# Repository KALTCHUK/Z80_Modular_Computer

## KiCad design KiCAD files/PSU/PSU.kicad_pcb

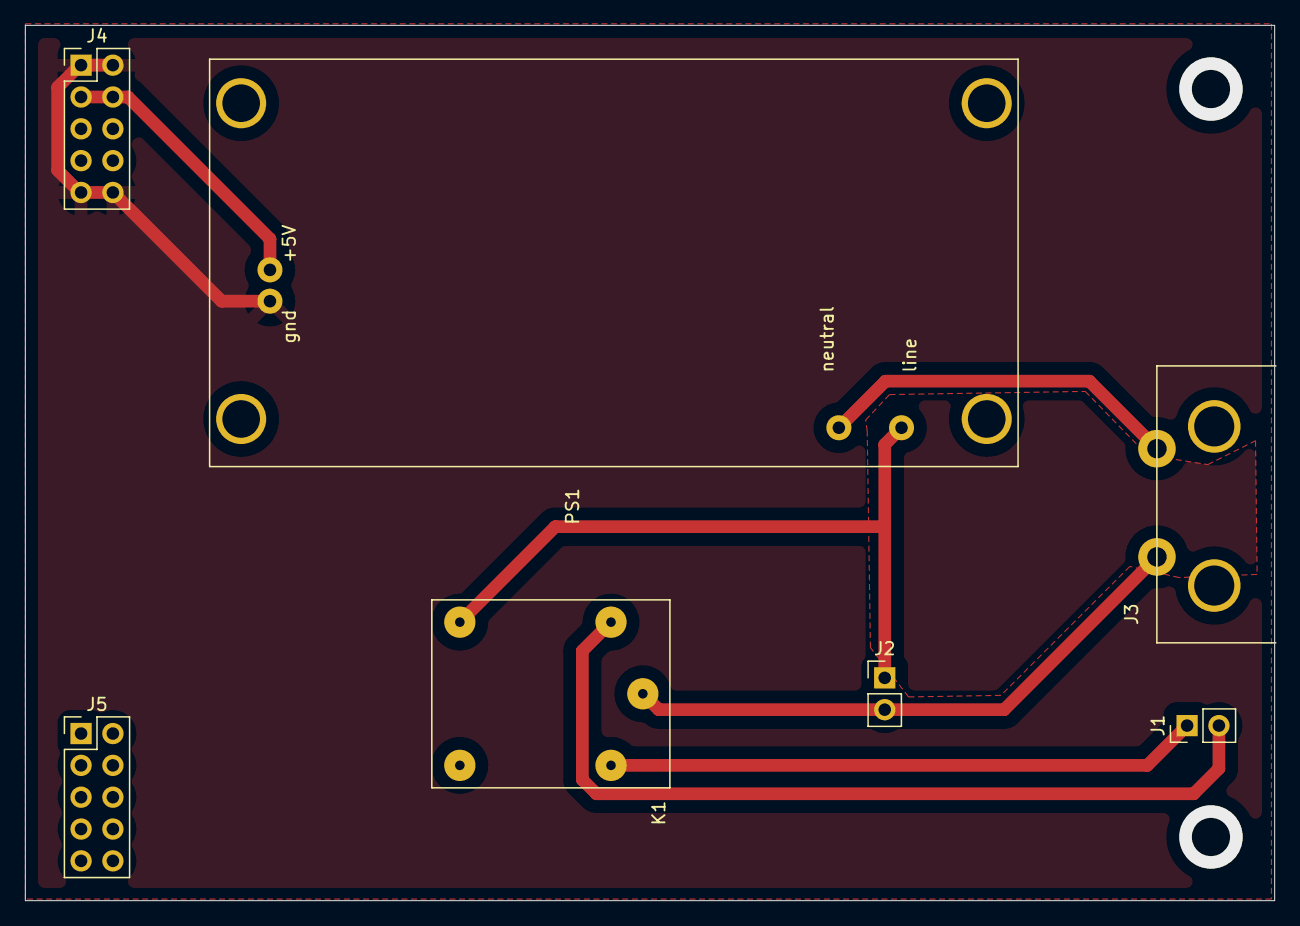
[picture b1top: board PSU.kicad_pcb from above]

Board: 2 copper layers, 99.7 x 69.8 mm, 7 parts (0 on the bottom side), 7 nets.

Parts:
J1: Ext power on; PinHeader_1x02_P2.54mm_Vertical
J2: Power switch; PinHeader_1x02_P2.54mm_Vertical
J3: Mains; IEC60320_2pin
J4: Power bus; PinHeader_2x05_P2.54mm_Vertical
J5: Mech support; PinHeader_2x05_P2.54mm_Vertical
K1: SRD-05VDC-SL-C; Relay_SPDT_Songel-15x19mm
PS1: XPJ-01B_5V_10W; Converter_ACDC_5V_10W_XPJ-01B

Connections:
GNDREF: J4.1, J4.2, J4.9, J4.10, PS1.3 (-Vo)
LINE: J2.2, J3.2, K1.5
NEUT: J3.1, PS1.1 (AC/N)
unnamed: J1.1, K1.4
unnamed: J1.2, K1.3
unnamed: J2.1, K1.1, PS1.2 (AC/L)
unnamed: J4.3, J4.4, PS1.4 (+Vo)

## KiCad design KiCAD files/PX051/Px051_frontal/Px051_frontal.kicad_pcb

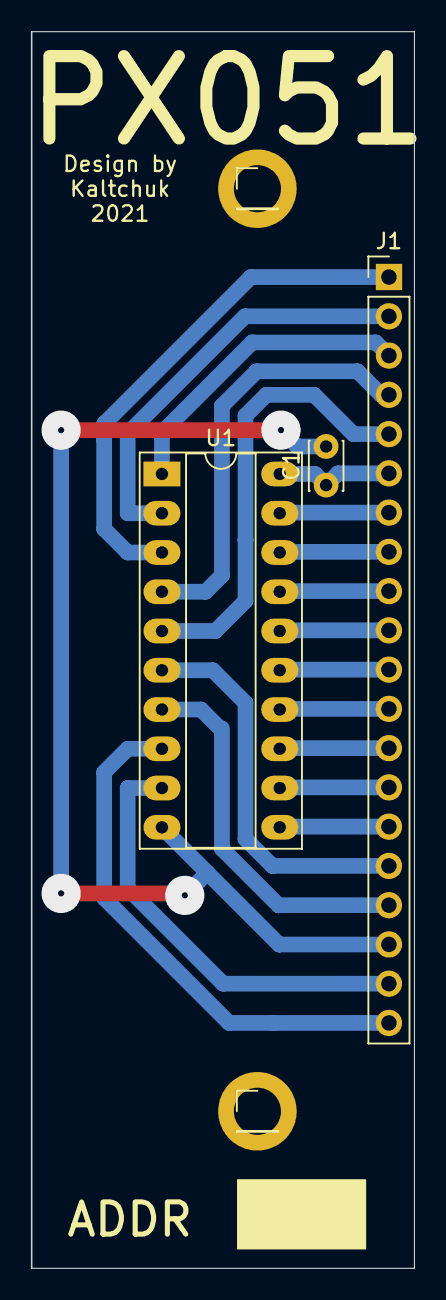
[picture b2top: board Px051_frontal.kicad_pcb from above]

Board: 2 copper layers, 24.8 x 80.0 mm, 5 parts (0 on the bottom side), 20 nets.

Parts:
C1: 10nF; C_Disc_D3.0mm_W2.0mm_P2.50mm
J1: Conn_01x20_Male; PinHeader_1x20_P2.54mm_Vertical
J7, J8: fixing bolt; PinHeader_1x01_P2.54mm_Vertical
U1: AT89C4051-24P; DIP-20_W7.62mm_Socket_LongPads

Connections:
GND: C1.2, J1.18, U1.10 (GND)
unnamed: C1.1, J1.6, U1.20 (VCC)
unnamed: J1.1, U1.3 (P3.1)
unnamed: J1.2, U1.2 (P3.0)
unnamed: J1.3, U1.1 (RST/VPP)
unnamed: J1.4, U1.4 (XTAL2)
unnamed: J1.5, U1.5 (XTAL1)
unnamed: J1.7, U1.19 (P1.7)
unnamed: J1.8, U1.18 (P1.6)
unnamed: J1.9, U1.17 (P1.5)
unnamed: J1.10, U1.16 (P1.4)
unnamed: J1.11, U1.15 (P1.3)
unnamed: J1.12, U1.14 (P1.2)
unnamed: J1.13, U1.13 (P1.1)
unnamed: J1.14, U1.12 (P1.0)
unnamed: J1.15, U1.11 (P3.7)
unnamed: J1.16, U1.6 (P3.2)
unnamed: J1.17, U1.7 (P3.3)
unnamed: J1.19, U1.9 (P3.5)
unnamed: J1.20, U1.8 (P3.4)

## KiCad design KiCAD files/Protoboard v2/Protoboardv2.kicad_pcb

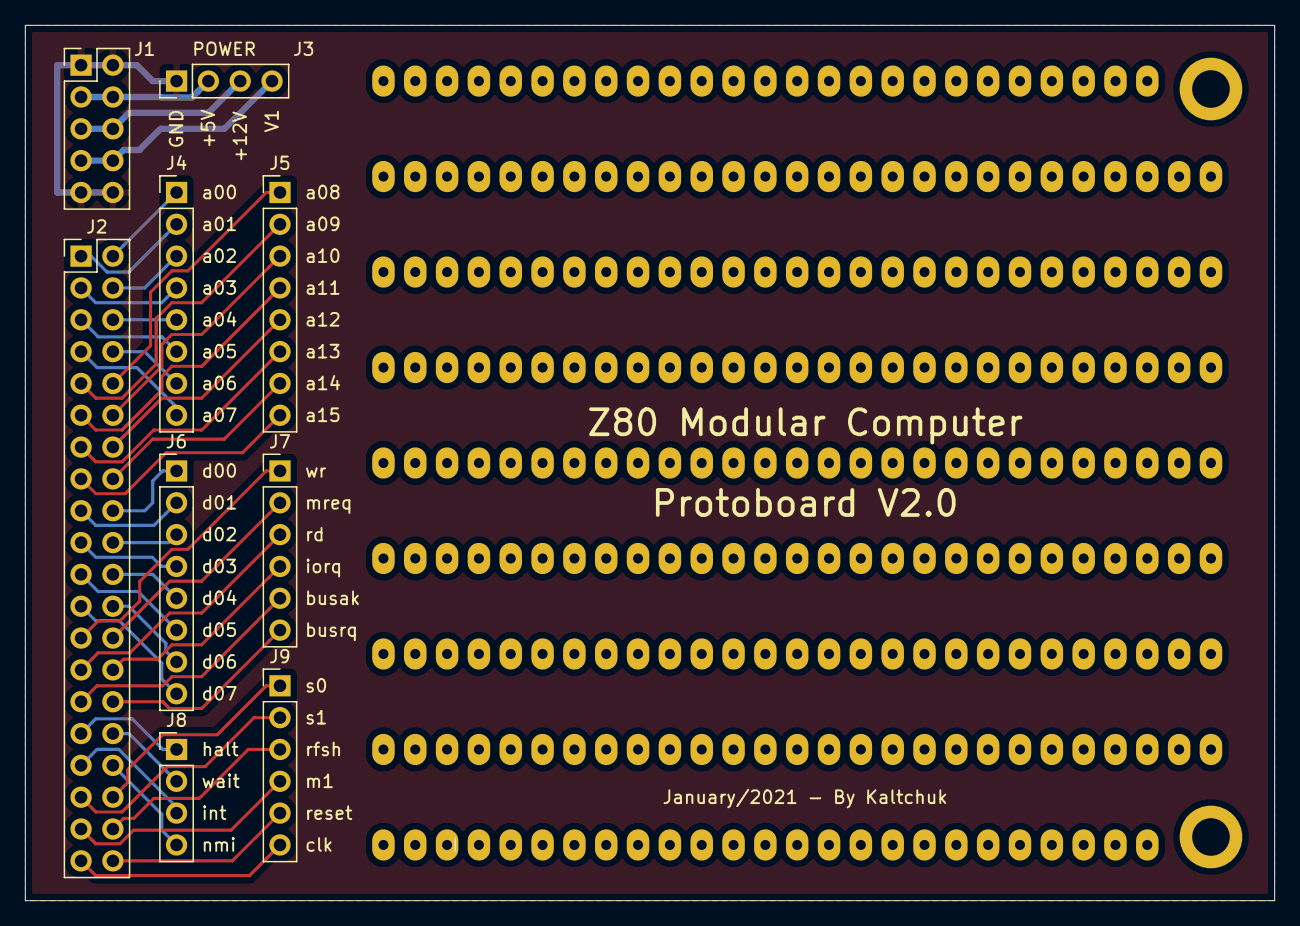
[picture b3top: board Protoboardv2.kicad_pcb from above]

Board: 2 copper layers, 99.7 x 69.8 mm, 9 parts (0 on the bottom side), 44 nets.

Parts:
J1: Conn_02x05; PinHeader_2x05_P2.54mm_Vertical
J2: Conn_02x20; PinHeader_2x20_P2.54mm_Vertical
J3, J8: Conn_01x04; PinHeader_1x04_P2.54mm_Vertical
J4, J5, J6: Conn_01x08; PinHeader_1x08_P2.54mm_Vertical
J7, J9: Conn_01x06; PinHeader_1x06_P2.54mm_Vertical

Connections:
/+5V: J1.3, J1.4, J3.2
/+12V: J1.5, J1.6, J3.3
/a00: J2.2, J4.1
/a01: J2.1, J4.2
/a02: J2.4, J4.3
/a03: J2.3, J4.4
/a04: J2.6, J4.5
/a05: J2.5, J4.6
/a06: J2.8, J4.7
/a07: J2.7, J4.8
/a08: J2.10, J5.1
/a09: J2.9, J5.2
/a10: J2.12, J5.3
/a11: J2.11, J5.4
/a12: J2.14, J5.5
/a13: J2.13, J5.6
/a14: J2.16, J5.7
/a15: J2.15, J5.8
/busack: J2.29, J7.5
/busrq: J2.30, J7.6
/clk: J2.39, J9.6
/d00: J2.18, J6.1
/d01: J2.17, J6.2
/d02: J2.20, J6.3
/d03: J2.19, J6.4
/d04: J2.22, J6.5
/d05: J2.21, J6.6
/d06: J2.24, J6.7
/d07: J2.23, J6.8
/gnd: J1.1, J1.2, J1.9, J1.10, J3.1
/halt: J2.31, J8.1
/int: J2.33, J8.3
/iorq: J2.28, J7.4
/m1: J2.37, J9.4
/mreq: J2.26, J7.2
/nmi: J2.34, J8.4
/rd: J2.27, J7.3
/reset: J2.40, J9.5
/rfsh: J2.38, J9.3
/s0: J2.36, J9.1
/s1: J2.35, J9.2
/v1: J1.7, J1.8, J3.4
/wait: J2.32, J8.2
/wr: J2.25, J7.1

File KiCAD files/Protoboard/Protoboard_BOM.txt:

J1	Power Bus	Connector_PinHeader_2.54mm:PinHeader_2x05_P2.54mm_Vertical	~	1
    J2	Signal Bus	Connector_PinHeader_2.54mm:PinHeader_2x20_P2.54mm_Vertical	~	1
    J3	Power	Connector_PinHeader_2.54mm:PinHeader_1x04_P2.54mm_Vertical	~	1
    J4	ADDR LO	Connector_PinHeader_2.54mm:PinHeader_1x08_P2.54mm_Vertical	~	1
    J5	ADDR HI	Connector_PinHeader_2.54mm:PinHeader_1x08_P2.54mm_Vertical	~	1
    J6	DATA	Connector_PinHeader_2.54mm:PinHeader_1x08_P2.54mm_Vertical	~	1
    J7	BUS CTRL	Connector_PinHeader_2.54mm:PinHeader_1x06_P2.54mm_Vertical	~	1
    J8	TIME CTRL	Connector_PinHeader_2.54mm:PinHeader_1x04_P2.54mm_Vertical	~	1
    J9	AUX SIGNAL	Connector_PinHeader_2.54mm:PinHeader_1x06_P2.54mm_Vertical	~	1

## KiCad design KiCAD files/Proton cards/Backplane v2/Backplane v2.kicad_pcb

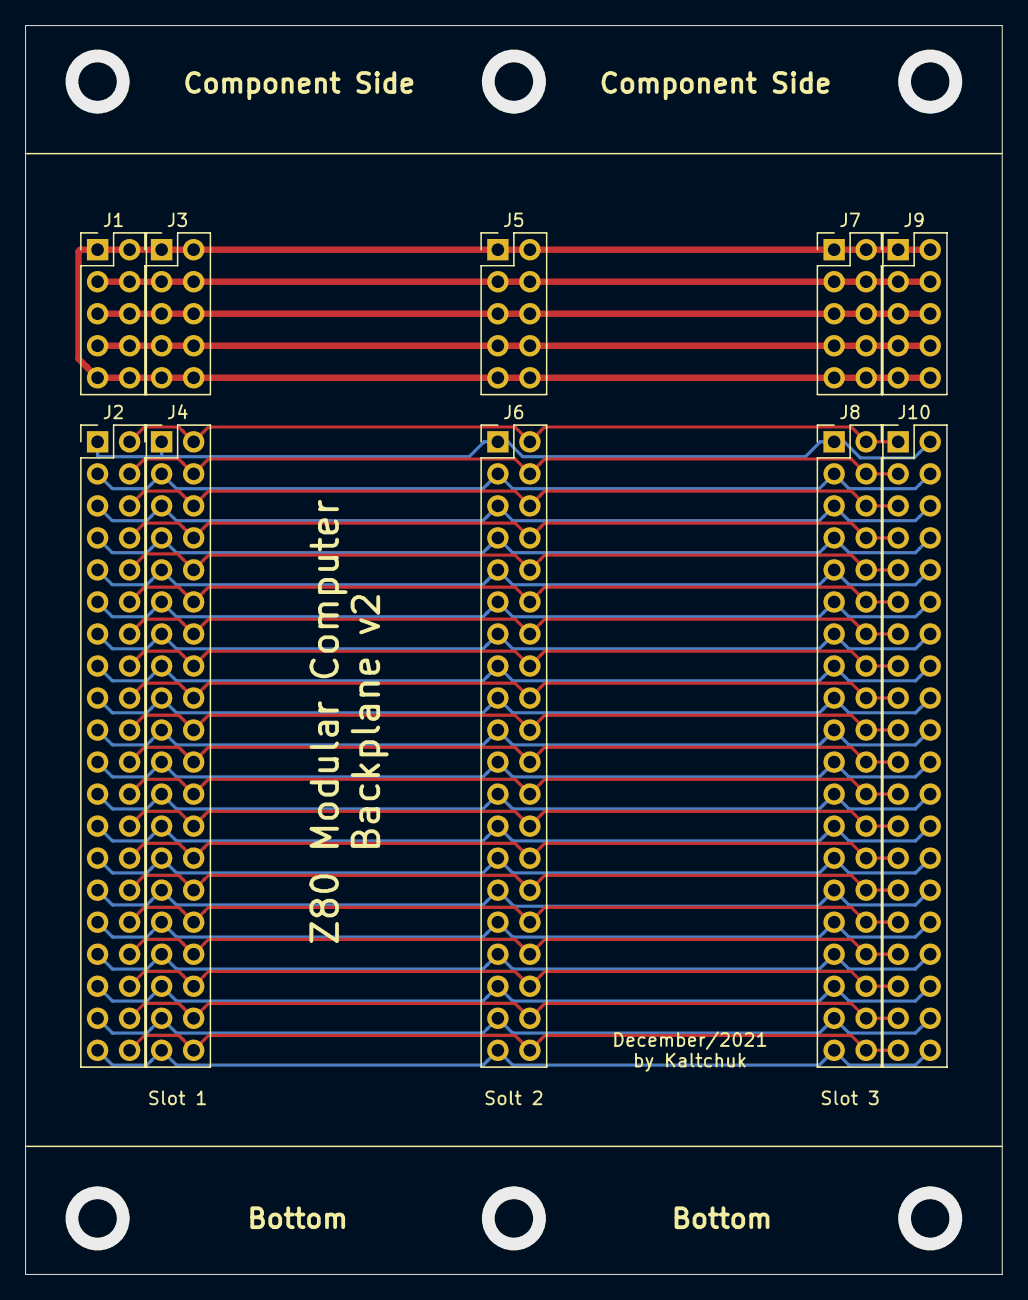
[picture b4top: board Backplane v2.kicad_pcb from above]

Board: 2 copper layers, 77.5 x 99.1 mm, 10 parts (0 on the bottom side), 44 nets.

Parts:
J1, J3, J5, J7, J9: Conn_02x05_Odd_Even; PinHeader_2x05_P2.54mm_Vertical
J2, J4, J6, J8, J10: Conn_02x20_Odd_Even; PinHeader_2x20_P2.54mm_Vertical

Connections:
/+5V: J1.3, J1.4, J3.3, J3.4, J5.3, J5.4, J7.3, J7.4, J9.3, J9.4
/+12V: J1.5, J1.6, J3.5, J3.6, J5.5, J5.6, J7.5, J7.6, J9.5, J9.6
/a00: J2.1, J4.1, J6.1, J8.1, J10.2
/a01: J2.2, J4.2, J6.2, J8.2, J10.1
/a02: J2.3, J4.3, J6.3, J8.3, J10.4
/a03: J2.4, J4.4, J6.4, J8.4, J10.3
/a04: J2.5, J4.5, J6.5, J8.5, J10.6
/a05: J2.6, J4.6, J6.6, J8.6, J10.5
/a06: J2.7, J4.7, J6.7, J8.7, J10.8
/a07: J2.8, J4.8, J6.8, J8.8, J10.7
/a08: J2.9, J4.9, J6.9, J8.9, J10.10
/a09: J2.10, J4.10, J6.10, J8.10, J10.9
/a10: J2.11, J4.11, J6.11, J8.11, J10.12
/a11: J2.12, J4.12, J6.12, J8.12, J10.11
/a12: J2.13, J4.13, J6.13, J8.13, J10.14
/a13: J2.14, J4.14, J6.14, J8.14, J10.13
/a14: J2.15, J4.15, J6.15, J8.15, J10.16
/a15: J2.16, J4.16, J6.16, J8.16, J10.15
/busack: J2.30, J4.30, J6.30, J8.30, J10.29
/busrq: J2.29, J4.29, J6.29, J8.29, J10.30
/clk: J2.40, J4.40, J6.40, J8.40, J10.39
/d00: J2.17, J4.17, J6.17, J8.17, J10.18
/d01: J2.18, J4.18, J6.18, J8.18, J10.17
/d02: J2.19, J4.19, J6.19, J8.19, J10.20
/d03: J2.20, J4.20, J6.20, J8.20, J10.19
/d04: J2.21, J4.21, J6.21, J8.21, J10.22
/d05: J2.22, J4.22, J6.22, J8.22, J10.21
/d06: J2.23, J4.23, J6.23, J8.23, J10.24
/d07: J2.24, J4.24, J6.24, J8.24, J10.23
/gnd: J1.1, J1.2, J1.9, J1.10, J3.1, J3.2, J3.9, J3.10, J5.1, J5.2, J5.9, J5.10, J7.1, J7.2, J7.9, J7.10, J9.1, J9.2, J9.9, J9.10
/halt: J2.32, J4.32, J6.32, J8.32, J10.31
/int: J2.34, J4.34, J6.34, J8.34, J10.33
/iorq: J2.27, J4.27, J6.27, J8.27, J10.28
/m1: J2.38, J4.38, J6.38, J8.38, J10.37
/mreq: J2.25, J4.25, J6.25, J8.25, J10.26
/nmi: J2.33, J4.33, J6.33, J8.33, J10.34
/rd: J2.28, J4.28, J6.28, J8.28, J10.27
/reset: J2.39, J4.39, J6.39, J8.39, J10.40
/s0: J2.35, J4.35, J6.35, J8.35, J10.36
/s1: J2.36, J4.36, J6.36, J8.36, J10.35
/s2: J2.37, J4.37, J6.37, J8.37, J10.38
/v1: J1.7, J1.8, J3.7, J3.8, J5.7, J5.8, J7.7, J7.8, J9.7, J9.8
/wait: J2.31, J4.31, J6.31, J8.31, J10.32
/wr: J2.26, J4.26, J6.26, J8.26, J10.25
